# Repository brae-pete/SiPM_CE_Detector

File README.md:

# SiPM Fluorescence Detector
Open Source Fluorescence Detector thas was applied for Capillary Electrophoresis. We noticed there was very little performance difference between the SiPM and the PMT when used in an epi-illumination setup. 

Included here is the KiCAD project folder, gerber files for PCB fabrication, STL files for 3D printed detector housing, list of materials for the circuit, an example electropherogram, and a jupyter notebook highlighting the data analysis. The project file 'Redraw' can be opened to view the circuit schematic. There are 2 PCB layout files, one for the 3 mm and one for the 6 mm sensor.

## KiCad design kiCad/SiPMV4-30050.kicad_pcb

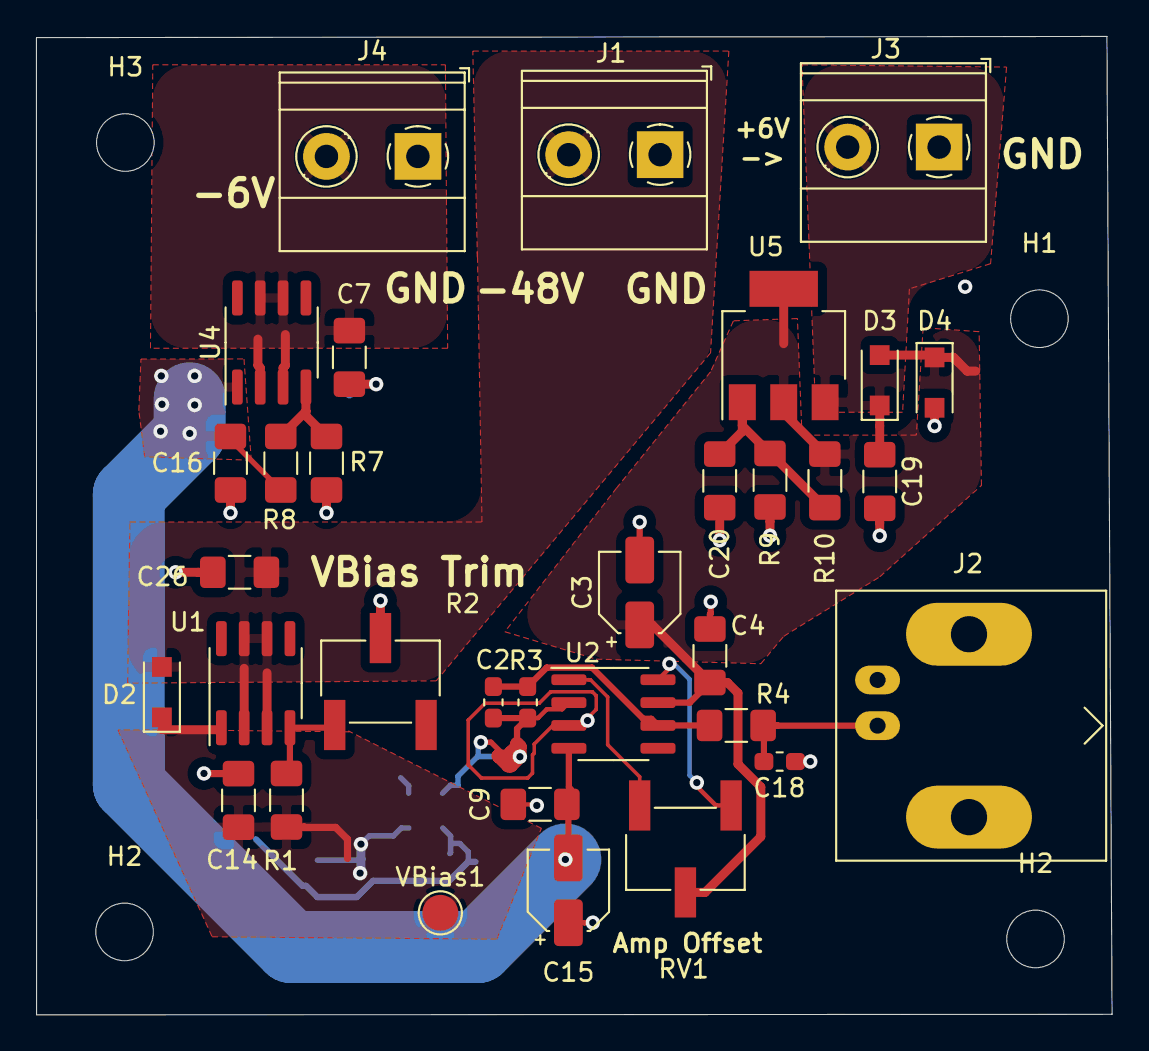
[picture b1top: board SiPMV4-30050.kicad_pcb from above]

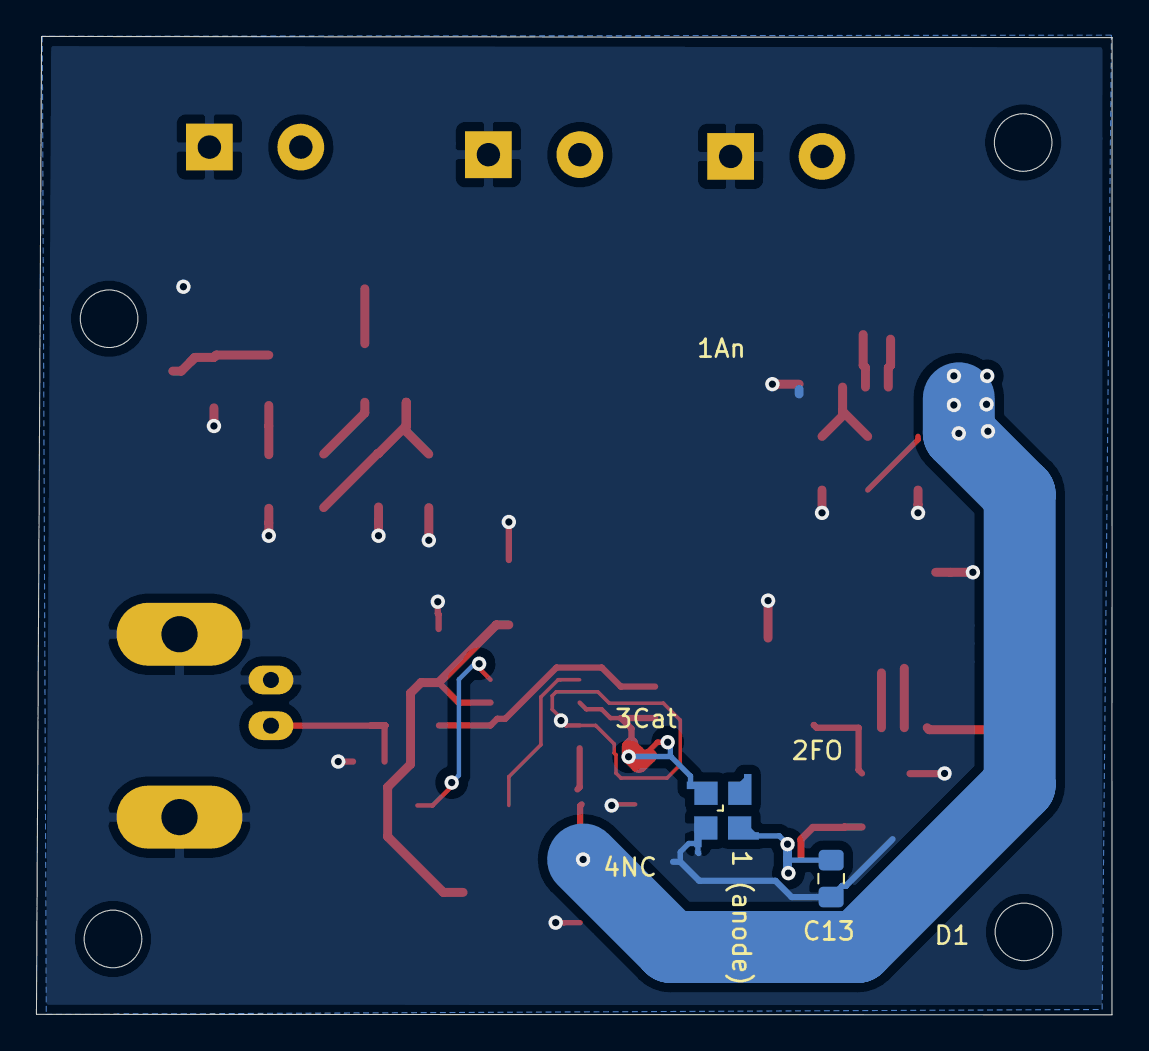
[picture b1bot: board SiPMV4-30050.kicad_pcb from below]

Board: 2 copper layers, 59.8 x 54.4 mm, 39 parts (2 on the bottom side), 15 nets.

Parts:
C2: 22p; C_0603_1608Metric_Pad1.05x0.95mm_HandSolder
C3, C15: 10uF; CP_Elec_4x3.9
C4, C9, C19: 0.1uF; C_1206_3216Metric_Pad1.42x1.75mm_HandSolder
C7, C14, C26: 1uF; C_1206_3216Metric_Pad1.42x1.75mm_HandSolder
C13: 10nF; C_0805_2012Metric_Pad1.15x1.40mm_HandSolder
C16, C20: 10uF; C_1206_3216Metric_Pad1.42x1.75mm_HandSolder
C18: 200n; C_0603_1608Metric_Pad1.05x0.95mm_HandSolder
D1: SiPM; Microfc_30050
D2, D3, D4: D; D_SOD-123F
H1, H2, H2#2, H3: MountingHole; MountingHole_3.2mm_M3
J1, J3, J4: Screw_Terminal_01x02; TerminalBlock_Phoenix_MKDS-1,5-2-5.08_1x02_P5.08mm_Horizont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
J2: Conn_Coaxial; BNC_Amphenol_B6252HB-NPP3G-50_Horizontal
R1: 240; R_1206_3216Metric_Pad1.42x1.75mm_HandSolder
R2: RTRIM (10k); Potentiometer_Bourns_3269W_Vertical
R3: 470; R_0603_1608Metric_Pad1.05x0.95mm_HandSolder
R4: 50; R_1206_3216Metric_Pad1.42x1.75mm_HandSolder
R7: 670; R_1206_3216Metric_Pad1.42x1.75mm_HandSolder
R8, R10: 210; R_1206_3216Metric_Pad1.42x1.75mm_HandSolder
R9: 700; R_1206_3216Metric_Pad1.42x1.75mm_HandSolder
RV1: R_POT_TRIM; Potentiometer_Bourns_3269W_Vertical
U1, U4: LM337L_SO8; SOIC-8_3.9x4.9mm_P1.27mm
U2: AD8675; SOIC-8_3.9x4.9mm_P1.27mm
U5: LM317_3PinPackage; SOT-223
VBias1: TestPoint; TestPoint_Pad_D2.0mm

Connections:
+5VA: C3.1, C4.2, D3.2, D4.1, R10.1, RV1.2, U2.7, U5.2, U5.4
+6V: C19.1, D3.1, J3.2, U5.3
+48V: C26.1, D2.2, J1.2, U1.2, U1.3, U1.6, U1.7
-5V: C9.1, C15.2, C16.2, R8.2, U2.4, U4.1
-6V: C7.2, J4.2, U4.2, U4.3, U4.6, U4.7
FB1: C2.2, R3.1, R4.1, U2.6
GND: C3.2, C4.1, C7.1, C9.2, C13.2, C14.1, C15.1, C16.1, C18.2, C19.2, C20.2, C26.2, D1.4, D4.2, J1.1, J2.2, J3.1, J4.1, R2.2, R7.1, R9.2, U2.3
unnamed: C2.1, D1.3, R3.2, U2.2
unnamed: C13.1, C14.2, D1.1, D2.1, R1.1, U1.1, U1.8, VBias1.1
unnamed: C18.1, J2.1, R4.2
unnamed: C20.1, R9.1, R10.2, U5.1
unnamed: R1.2, R2.1, U1.4
unnamed: R7.2, R8.1, U4.4
unnamed: RV1.1, U2.8
unnamed: RV1.3, U2.1

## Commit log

2020-05-22 KiCad Files
2020-05-22 Gerber Files
2020-05-22 CAD Files
2020-05-22 Digital Filter Workflow
2020-07-20 License
2020-07-20 List of Materials
2020-07-20 Image
    Image of the circuit.
